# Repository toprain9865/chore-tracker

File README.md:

# Chore Tracker

A device to track up to 5 chores around the house. I am currently tracking my clothes washer, clothes dryer, dishwasher, trash, and recycling. The indicators are WS2812 LEDs, allowing customization of the indicator colors, patterns, etc.

I have additionally included a DHT22 temperature and humidity sensor.

## Code

I used ESPHome and Home Assistant to do all the heavy lifting. You can find the basic code to get everything on the PCB into an ESPHome configuration.

## Body

The body is deep enough to comfortably hold all the components as well as a generous amount of extra wire, in case you don't want to deal with getting everything the perfect length and just so. The hole in the model for the USB cord will fit a cord, but won't fit a terminated cord. You'll have to pull it through and then add the JST connector.

## PCB

When soldering the PCB, don't skimp out on the pin sockets. Both the ground and power planes are directly under the antenna, which isn't a performance issue if you use the pin sockets to get enough of a separation. I don't know how it might work if you solder it directly to the board.

I also designed the PCB to include a potentiometer to control the brightness of the LEDs. I ended up not using it, and instead just programming a fixed brightness that works well for me. Optional components for the potentiometer are listed below *in italics*.

## BOM

|Qty|Description|P/N|
|-|-|-|
|1|PCB|
1|Printed case
1|USB power cable|
|2|JST connector, 1x3, 2.54mm pitch
|2|JST PCB header, 1x3, 2.54mm pitch
6|JST connector, 1x2, 2.54mm pitch
6|JST PCB header, 1x2, 2.54mm pitch
1|esp8266 microcontroller|WeMos D1 mini
1|I<sup>2</sup>C I/O expander|MCP23008
1|DIP18 IC socket
2|10k resistor, 1/4 W, axial, len: 9.0mm, dia: 3.2mm
5|SPST momentary push button, 6mm cap, 6.9mm thread
5|WS2812B 5050 neopixel LEDs with PCB|
1|DHT22 compatible temperature & humidity sensor|AM2302
1|*JST connector, 1x3, 2.54mm pitch*
1|*JST PCB header, 1x3, 2.54mm pitch*
1|*Potentiometer*

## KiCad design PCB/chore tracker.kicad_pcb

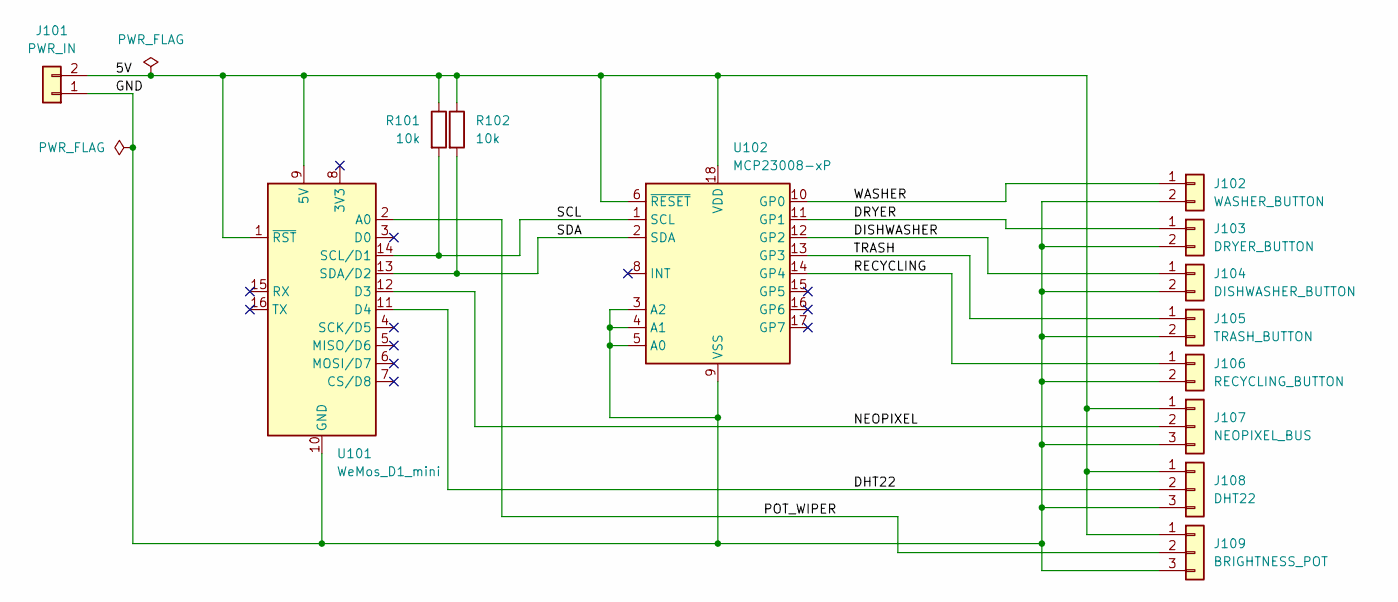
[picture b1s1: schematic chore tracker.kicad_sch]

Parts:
J101: PWR_IN; JST_XH_B2B-XH-AM_1x02_P2.50mm_Vertical
J102: WASHER_BUTTON; JST_XH_B2B-XH-AM_1x02_P2.50mm_Vertical
J103: DRYER_BUTTON; JST_XH_B2B-XH-AM_1x02_P2.50mm_Vertical
J104: DISHWASHER_BUTTON; JST_XH_B2B-XH-AM_1x02_P2.50mm_Vertical
J105: TRASH_BUTTON; JST_XH_B2B-XH-AM_1x02_P2.50mm_Vertical
J106: RECYCLING_BUTTON; JST_XH_B2B-XH-AM_1x02_P2.50mm_Vertical
J107: NEOPIXEL_BUS; JST_XH_B3B-XH-AM_1x03_P2.50mm_Vertical
J108: DHT22; JST_XH_B3B-XH-AM_1x03_P2.50mm_Vertical
J109: BRIGHTNESS_POT; JST_XH_B3B-XH-AM_1x03_P2.50mm_Vertical
R101, R102: 10k; R_Axial_DIN0309_L9.0mm_D3.2mm_P2.54mm_Vertical
U101: WeMos_D1_mini; WEMOS_D1_mini_light
U102: MCP23008-xP; DIP-18_W7.62mm

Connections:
/5V: J101.2, J107.1, J108.1, J109.1, R101.1, R102.1, U101.1 (~RST), U101.9 (5V), U102.6 (~RESET), U102.18 (VDD)
/DHT22: J108.2, U101.11 (D4)
/DISHWASHER: J104.1, U102.12 (GP2)
/DRYER: J103.1, U102.11 (GP1)
/GND: J101.1, J102.2, J103.2, J104.2, J105.2, J106.2, J107.3, J108.3, J109.3, U101.10 (GND), U102.3 (A2), U102.4 (A1), U102.5 (A0), U102.9 (VSS)
/NEOPIXEL: J107.2, U101.12 (D3)
/POT_WIPER: J109.2, U101.2 (A0)
/RECYCLING: J106.1, U102.14 (GP4)
/SCL: R101.2, U101.14 (SCL/D1), U102.1 (SCL)
/SDA: R102.2, U101.13 (SDA/D2), U102.2 (SDA)
/TRASH: J105.1, U102.13 (GP3)
/WASHER: J102.1, U102.10 (GP0)

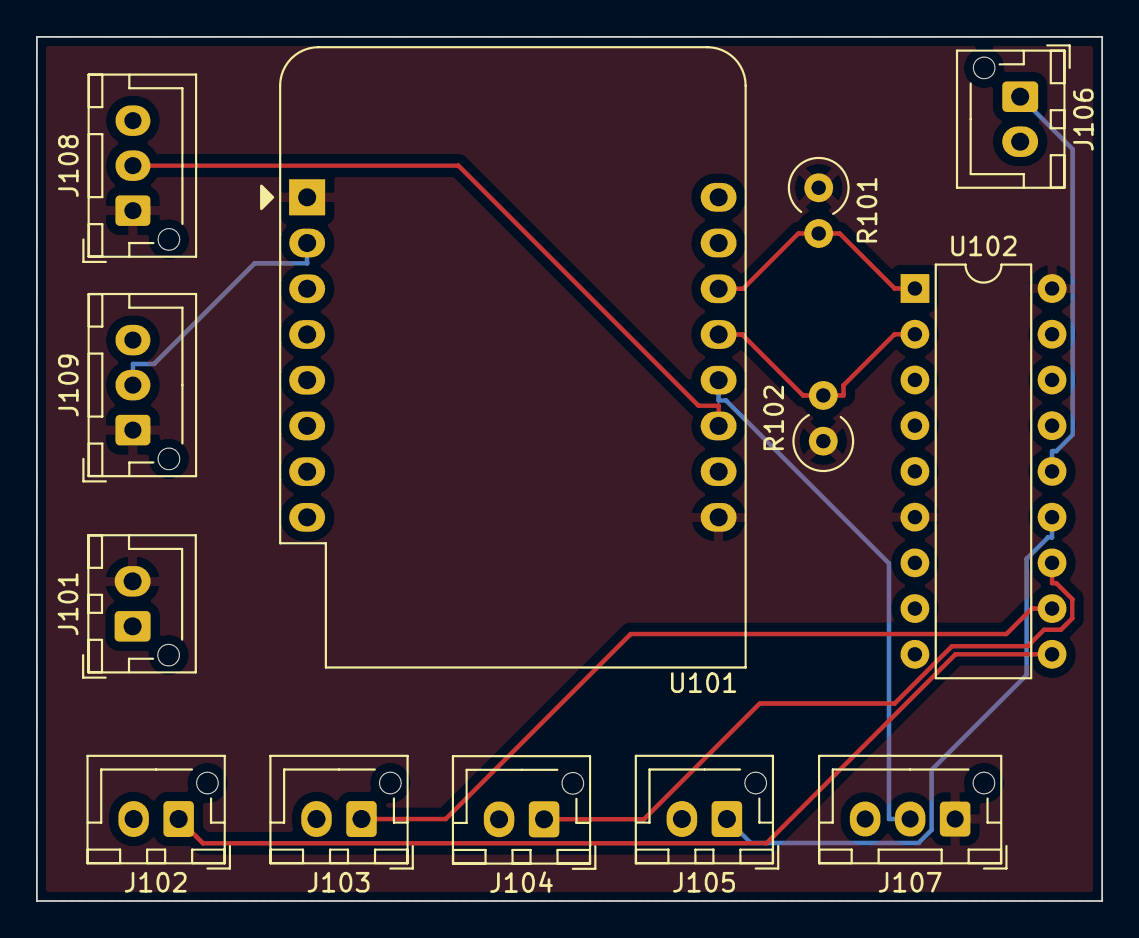
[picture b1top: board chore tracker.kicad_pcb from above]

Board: 2 copper layers, 59.2 x 48.0 mm, 13 parts (0 on the bottom side), 12 nets.

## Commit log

2023-02-28 formatting
2023-03-01 add BOM
2023-03-01 break out optional potentiometer components

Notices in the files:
README.md:
CC BY-NC-SA 4.0
